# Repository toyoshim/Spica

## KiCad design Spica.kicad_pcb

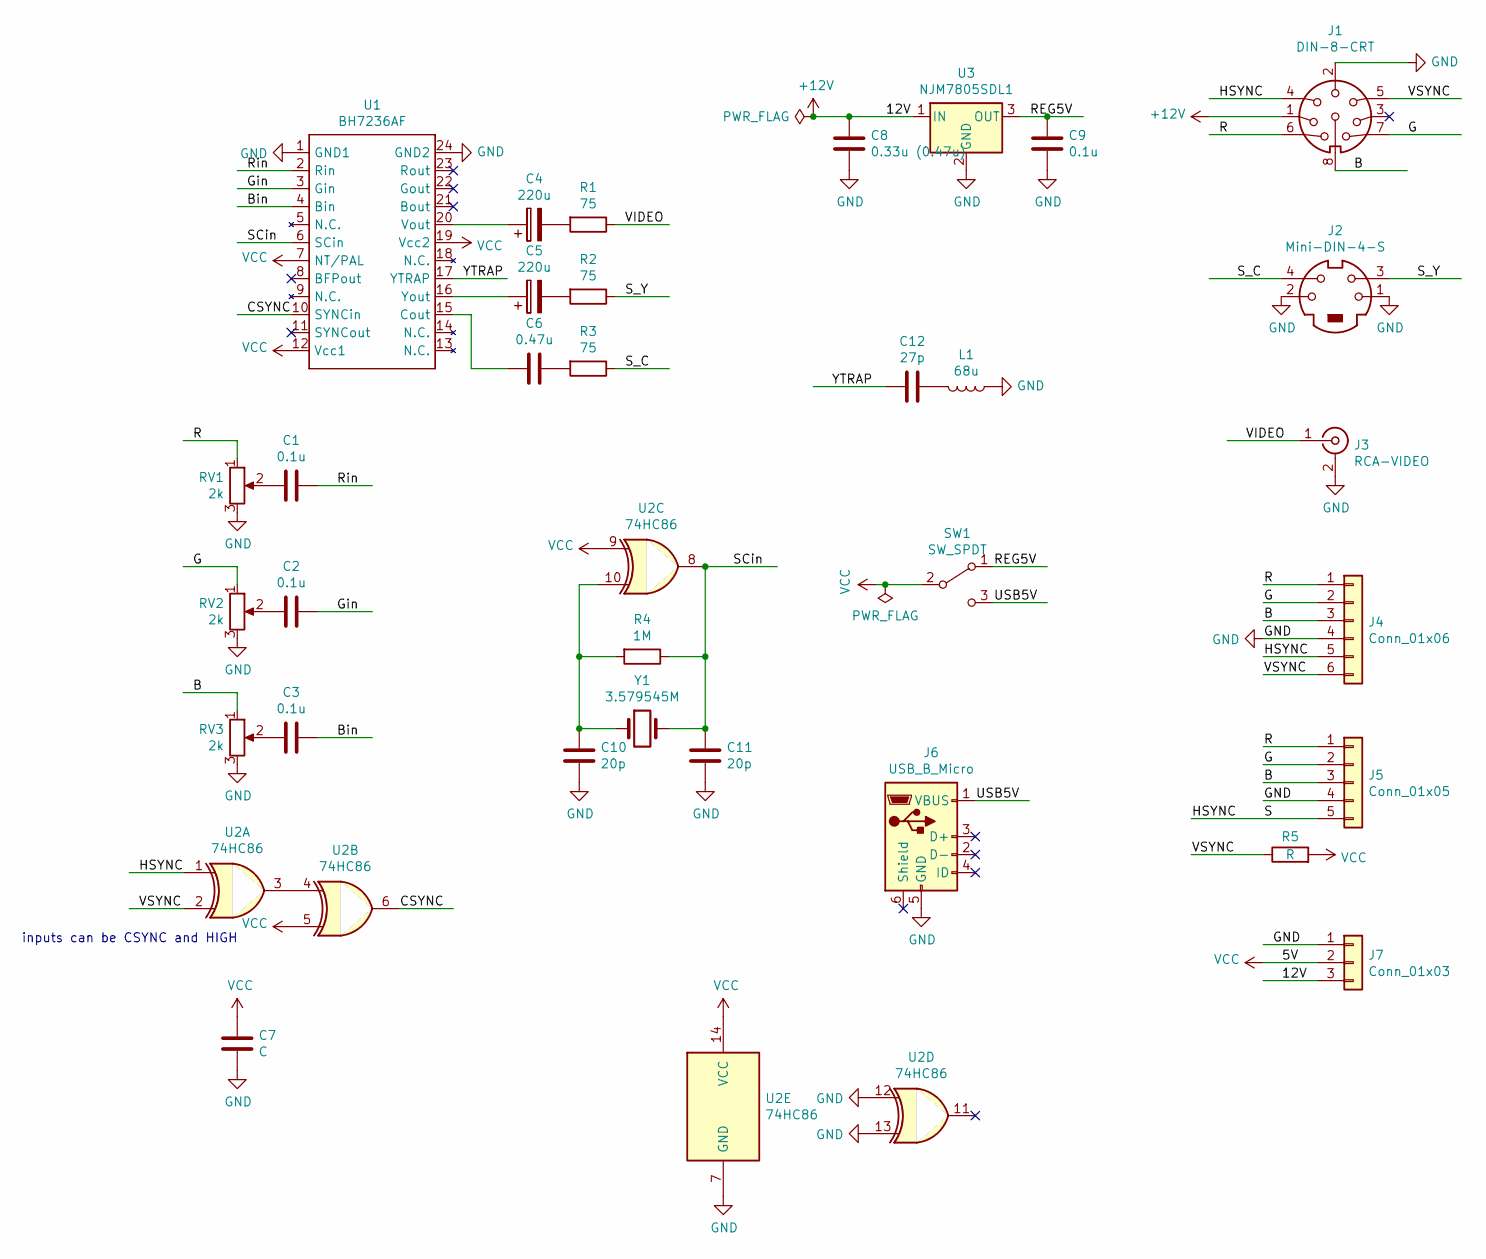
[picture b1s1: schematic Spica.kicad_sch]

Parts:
C1, C2, C3, C9: 0.1u; C_0603_1608Metric
C4, C5: 220u; CP_Radial_D5.0mm_P2.50mm
C6: 0.47u; C_0603_1608Metric
C7: C; C_0603_1608Metric
C8: 0.33u (0.47u); C_0603_1608Metric
C10, C11: 20p; C_0603_1608Metric
C12: 27p; C_0603_1608Metric
J1: DIN-8-CRT; DIN8_Conn_Female_RTC9016
J2: Mini-DIN-4-S; MINI-DIN-4-DI-6798-4
J3: RCA-VIDEO; RCA-HLR-3201VXB-002HG
J4: Conn_01x06; Molex_KK-254_AE-6410-06A_1x06_P2.54mm_Vertical
J5: Conn_01x05; Molex_SPOX_05_P5.00mm
J6: USB_B_Micro; MicroUSB_ZX62R-B-5P
J7: Conn_01x03; PinHeader_1x03_P2.54mm_Vertical
L1: 68u; L_0805_2012Metric
R1, R2, R3: 75; R_0603_1608Metric
R4: 1M; R_0603_1608Metric
R5: R; R_0603_1608Metric
RV1, RV2, RV3: 2k; RV-RM-065
SW1: SW_SPDT; PinHeader_1x03_P2.54mm_Vertical
U1: BH7236AF; SOIC-24_4.4x15.4mm_P1.27mm
U2: 74HC86; SOIC-14_3.9x8.7mm_P1.27mm
U3: NJM7805SDL1; TO-252-2
Y1: 3.579545M; Crystal_HC49-4H_Vertical

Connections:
+12V: C8.2, J1.1, J7.3, U3.1 (IN)
/B: J1.8, J4.3, J5.3, RV3.1
/Bin: C3.1, U1.4 (Bin)
/CSYNC: U1.10 (SYNCin), U2.6
/G: J1.7, J4.2, J5.2, RV2.1
/Gin: C2.1, U1.3 (Gin)
/HSYNC: J1.4, J4.5, J5.5, U2.1
/R: J1.6, J4.1, J5.1, RV1.1
/REG5V: C9.2, SW1.1 (A), U3.3 (OUT)
/Rin: C1.1, U1.2 (Rin)
/SCin: C11.1, R4.1, U1.6 (SCin), U2.8, Y1.2
/S_C: J2.4, R3.1
/S_Y: J2.3, R2.1
/USB5V: J6.1 (VBUS), SW1.3 (C)
/VIDEO: J3.1 (In), R1.1
/VSYNC: J1.5, J4.6, R5.1, U2.2
/YTRAP: C12.2, U1.17 (YTRAP)
GND: C7.2, C8.1, C9.1, C10.2, C11.2, J1.2, J2.1, J2.2, J3.2 (Ext), J4.4, J5.4, J6.5 (GND), J7.1, L1.1, RV1.3, RV2.3, RV3.3, U1.1 (GND1), U1.24 (GND2), U2.7 (GND), U2.12, U2.13, U3.2 (GND)
unnamed: C1.2, RV1.2
unnamed: C2.2, RV2.2
unnamed: C3.2, RV3.2
unnamed: C4.1, U1.20 (Vout)
unnamed: C4.2, R1.2
unnamed: C5.1, U1.16 (Yout)
unnamed: C5.2, R2.2
unnamed: C6.1, R3.2
unnamed: C6.2, U1.15 (Cout)
unnamed: C10.1, R4.2, U2.10, Y1.1
unnamed: C12.1, L1.2
unnamed: U2.3, U2.4
VCC: C7.1, J7.2, R5.2, SW1.2 (B), U1.7 (NT/PAL), U1.12 (Vcc1), U1.19 (Vcc2), U2.5, U2.9, U2.14 (VCC)

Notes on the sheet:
inputs can be CSYNC and HIGH

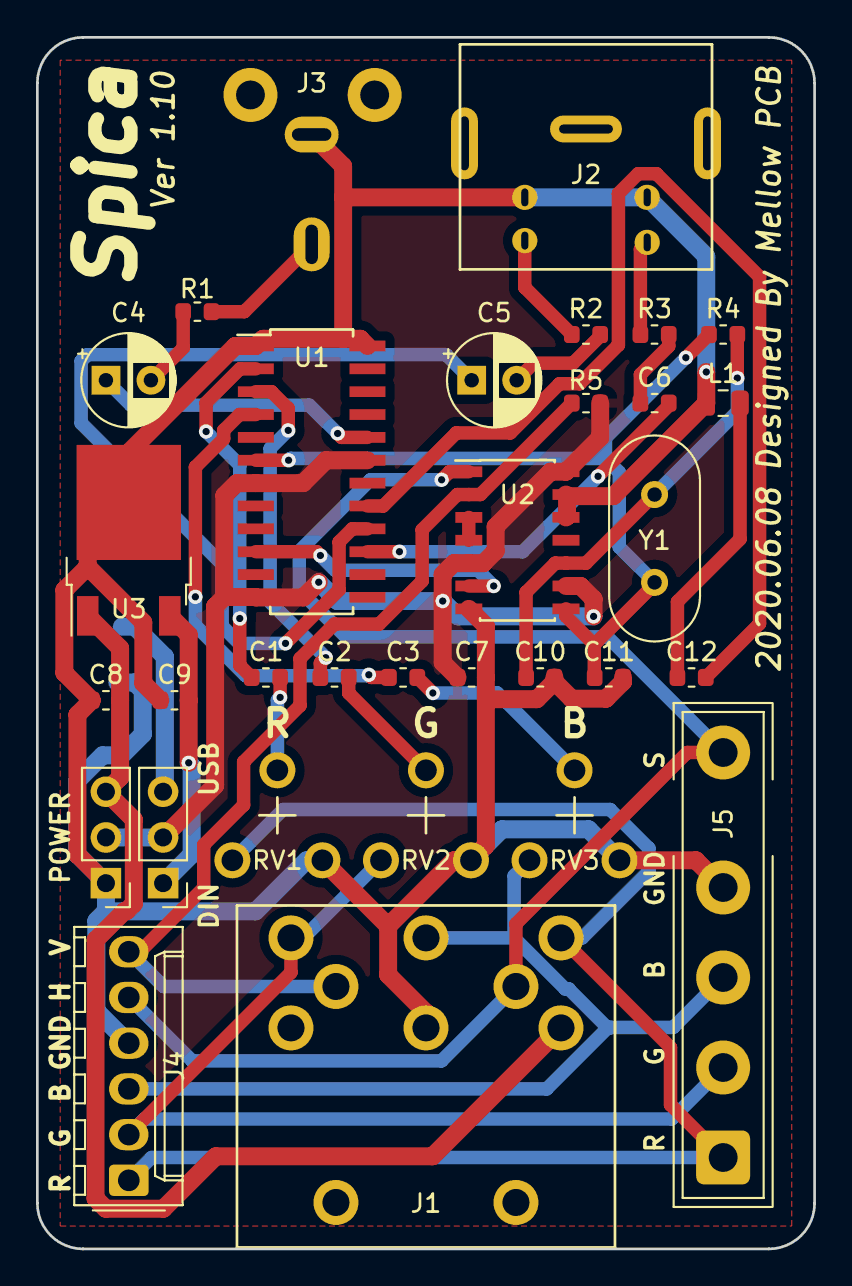
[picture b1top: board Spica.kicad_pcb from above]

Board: 2 copper layers, 43.2 x 67.3 mm, 33 parts (1 on the bottom side), 31 nets.
